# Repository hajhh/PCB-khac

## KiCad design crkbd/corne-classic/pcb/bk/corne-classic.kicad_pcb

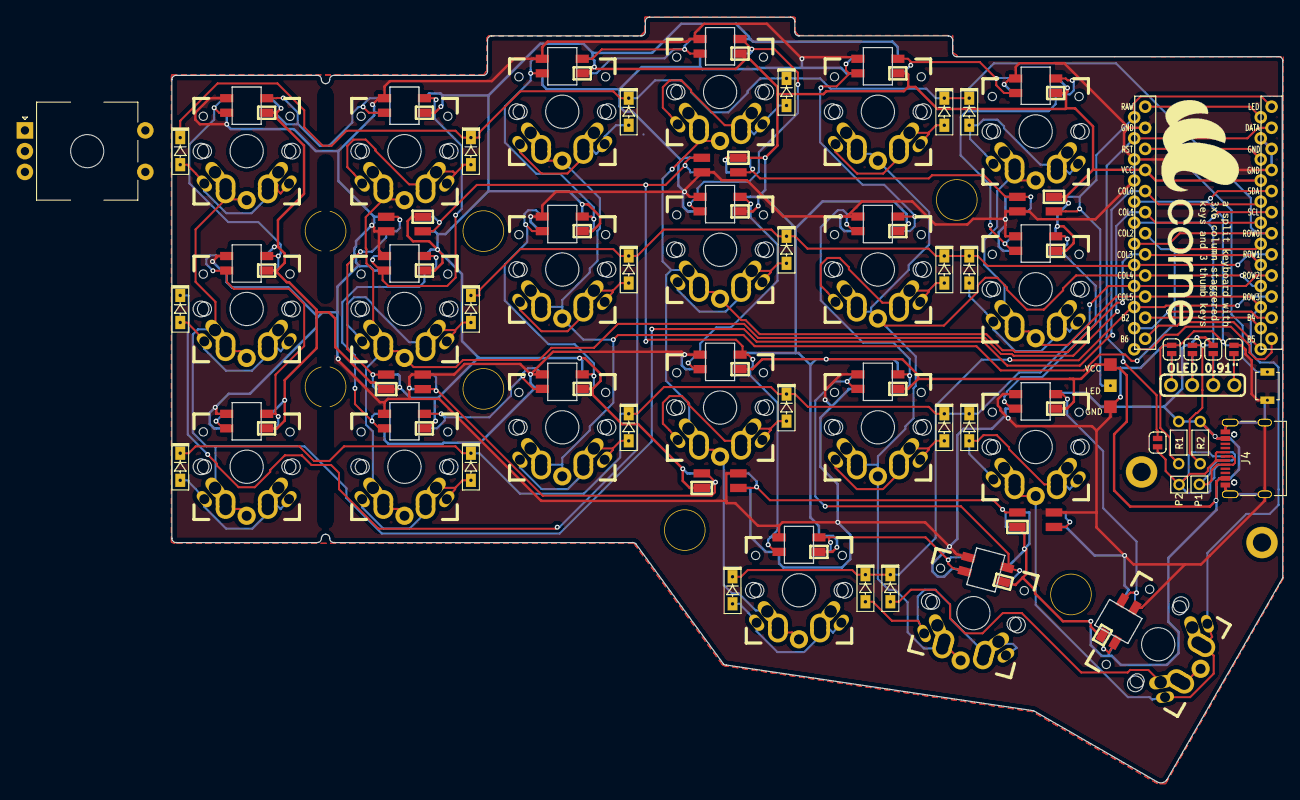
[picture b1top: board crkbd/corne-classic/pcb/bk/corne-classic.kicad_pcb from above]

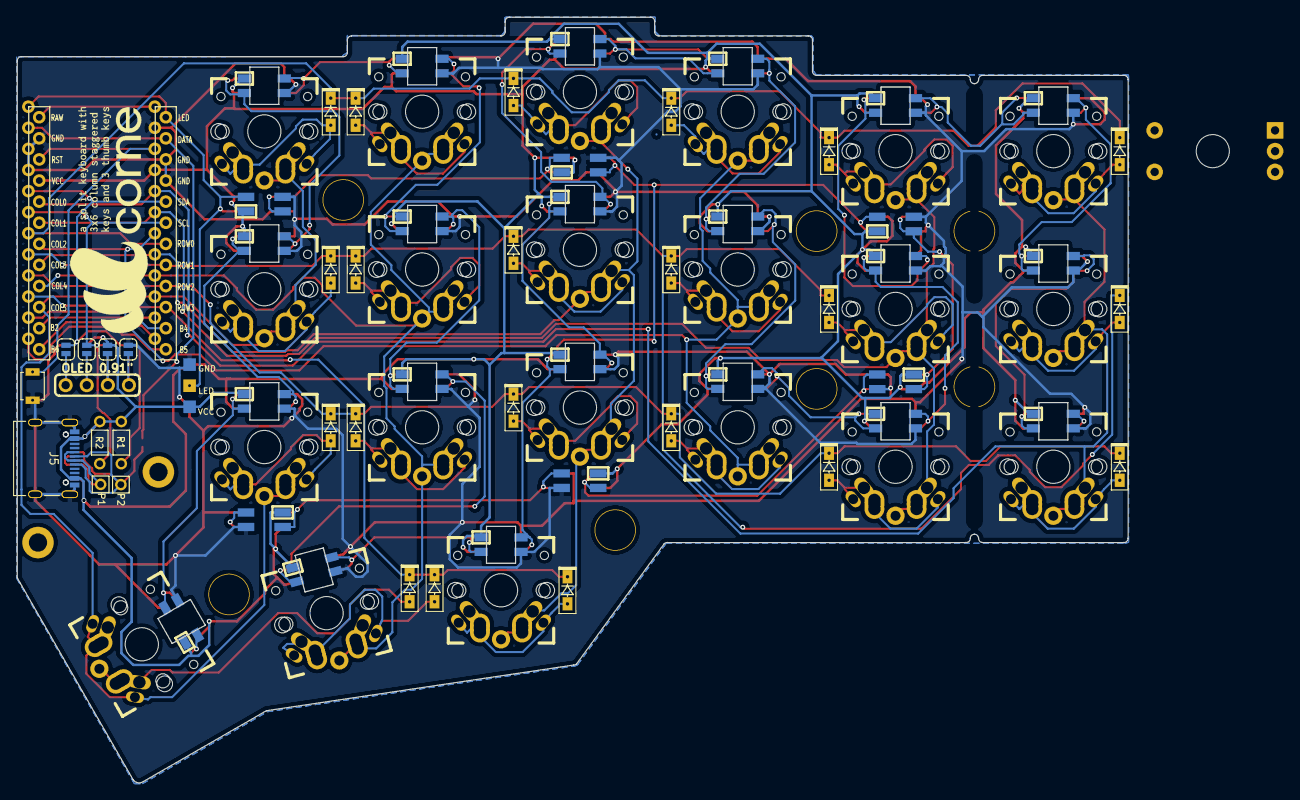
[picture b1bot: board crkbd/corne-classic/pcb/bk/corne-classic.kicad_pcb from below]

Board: 2 copper layers, 133.8 x 92.2 mm, 104 parts (7 on the bottom side), 68 nets.

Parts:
D1, D2, D3, D4, D5, D6, D7, D8, D9, D10, D11, D12, D13, D14, D15, D16, D17, D18, D19, D20, D21: D; Diode_smd
H1, H2: Hole_M2
H3, H4, H5, H6, H7, H8, H9: HOLE
H10, H11: logo
H12, H13, H14, H15: hole2
J2: OLED; OLED_SPILT
J3: LED; StripLED_rev
J4, J5: USB_C_Receptacle_Palconn_UTC16-G
JP1, JP2, JP3, JP4, JP5, JP6, JP7, JP8, JP9: jp
L1, L2, L3, L4, L5, L6: SK6812MINI; SK6812MINI_underglow_rev
L7, L8, L9, L10, L11, L12, L13, L14, L15, L16, L17, L18, L19, L20, L21, L22, L23, L24, L25, L26, L27: SK6812MINI; SK6812MINI_rev
P1, P2: i2c-pin; 1pin_conn
R1, R2: R
RSW1: SW_PUSH; SW_SPST_B3U-1000P
SW1, SW2, SW3, SW4, SW5, SW6, SW7, SW8, SW9, SW10, SW11, SW12, SW13, SW14, SW15, SW16, SW17, SW18, SW19, SW20: SW_PUSH; 1u
SW21: SW_PUSH; 1.75u
SW22: Rotary_Encoder_Switch; Rotary_econder
U1: ProMicro; ProMicro_v2

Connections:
GND: J3.1, J4.A1, J4.A12, J4.B1, J4.B12, J4.S1, J5.A1, J5.A12, J5.B1, J5.B12, J5.S1, JP2.1, JP9.1, L1.2, L2.2, L3.2, L4.2, L5.2, L6.2, L7.2, L8.2, L9.2, L10.2, L11.2, L12.2, L13.2, L14.2, L15.2, L16.2, L17.2, L18.2, L19.2, L20.2, L21.2, L22.2, L23.2, L24.2, L25.2, L26.2, L27.2, RSW1.2, U1.3, U1.4, U1.23
LED: J3.2, L3.3, U1.1
unnamed: D1.2, SW1.2
unnamed: D2.2, SW2.2
unnamed: D3.2, SW3.2
unnamed: D4.2, SW4.2
unnamed: D5.2, SW5.2
unnamed: D6.2, SW6.2
unnamed: D7.2, SW7.2
unnamed: D8.2, SW8.2
unnamed: D9.2, SW9.2
unnamed: D10.2, SW10.2
unnamed: D11.2, SW11.2
unnamed: D12.2, SW12.2
unnamed: D13.2, SW13.2
unnamed: D14.2, SW14.2
unnamed: D15.2, SW15.2
unnamed: D16.2, SW16.2
unnamed: D17.2, SW17.2
unnamed: D18.2, SW18.2
unnamed: D19.2, SW19.2
unnamed: D20.2, SW20.2
unnamed: D21.2, SW21.2
unnamed: J2.1, JP5.2, JP9.2
unnamed: J2.2, JP4.2, JP8.2
unnamed: J2.3, JP3.2, JP7.2
unnamed: J2.4, JP2.2, JP6.2
unnamed: J4.A6, J4.B6, J5.A6, J5.B6, JP1.2, P2.1
unnamed: J4.A7, J4.B7, J5.A7, J5.B7, P1.1
unnamed: L7.3, L8.1
unnamed: L9.3, L10.1
unnamed: L10.3, L16.1
unnamed: L11.1, L17.3
unnamed: L11.3, L12.1
unnamed: L12.3, L18.1
unnamed: L13.1, L19.3
unnamed: L7.1, L13.3
unnamed: L8.3, L14.1
unnamed: L14.3, L20.1
unnamed: L15.1, L21.3
unnamed: L9.1, L15.3
unnamed: L16.3, L22.1
unnamed: L17.1, L23.3
unnamed: L18.3, L24.1
unnamed: L20.3, L21.1
unnamed: L1.1, L4.3
unnamed: L1.3, L2.1, L22.3, L25.1
unnamed: L23.1, L26.3
unnamed: L2.3, L3.1
unnamed: L24.3, L27.1
unnamed: L4.1, L5.3
unnamed: L25.3, L26.1
unnamed: L5.1, L6.3
SCL: JP4.1, JP7.1, R2.2, U1.6
SDA: JP5.1, JP6.1, R1.2, U1.5
VCC: J3.3, J4.A4, J4.A9, J4.B4, J4.B9, J5.A4, J5.A9, J5.B4, J5.B9, JP3.1, JP8.1, L1.4, L2.4, L3.4, L4.4, L5.4, L6.4, L7.4, L8.4, L9.4, L10.4, L11.4, L12.4, L13.4, L14.4, L15.4, L16.4, L17.4, L18.4, L19.4, L20.4, L21.4, L22.4, L23.4, L24.4, L25.4, L26.4, L27.4, R1.1, R2.1, U1.21
col0: SW1.1, SW7.1, SW13.1, U1.20
col1: SW2.1, SW8.1, SW14.1, U1.19
col2: SW3.1, SW9.1, SW15.1, U1.18
col3: SW4.1, SW10.1, SW16.1, SW19.1, U1.17
col4: SW5.1, SW11.1, SW17.1, SW20.1, U1.16
col5: SW6.1, SW12.1, SW18.1, SW21.1, U1.15
data: JP1.1, U1.2
reset: RSW1.1, U1.22
row0: D1.1, D2.1, D3.1, D4.1, D5.1, D6.1, U1.7
row1: D7.1, D8.1, D9.1, D10.1, D11.1, D12.1, U1.8
row2: D13.1, D14.1, D15.1, D16.1, D17.1, D18.1, U1.9
row3: D19.1, D20.1, D21.1, U1.10

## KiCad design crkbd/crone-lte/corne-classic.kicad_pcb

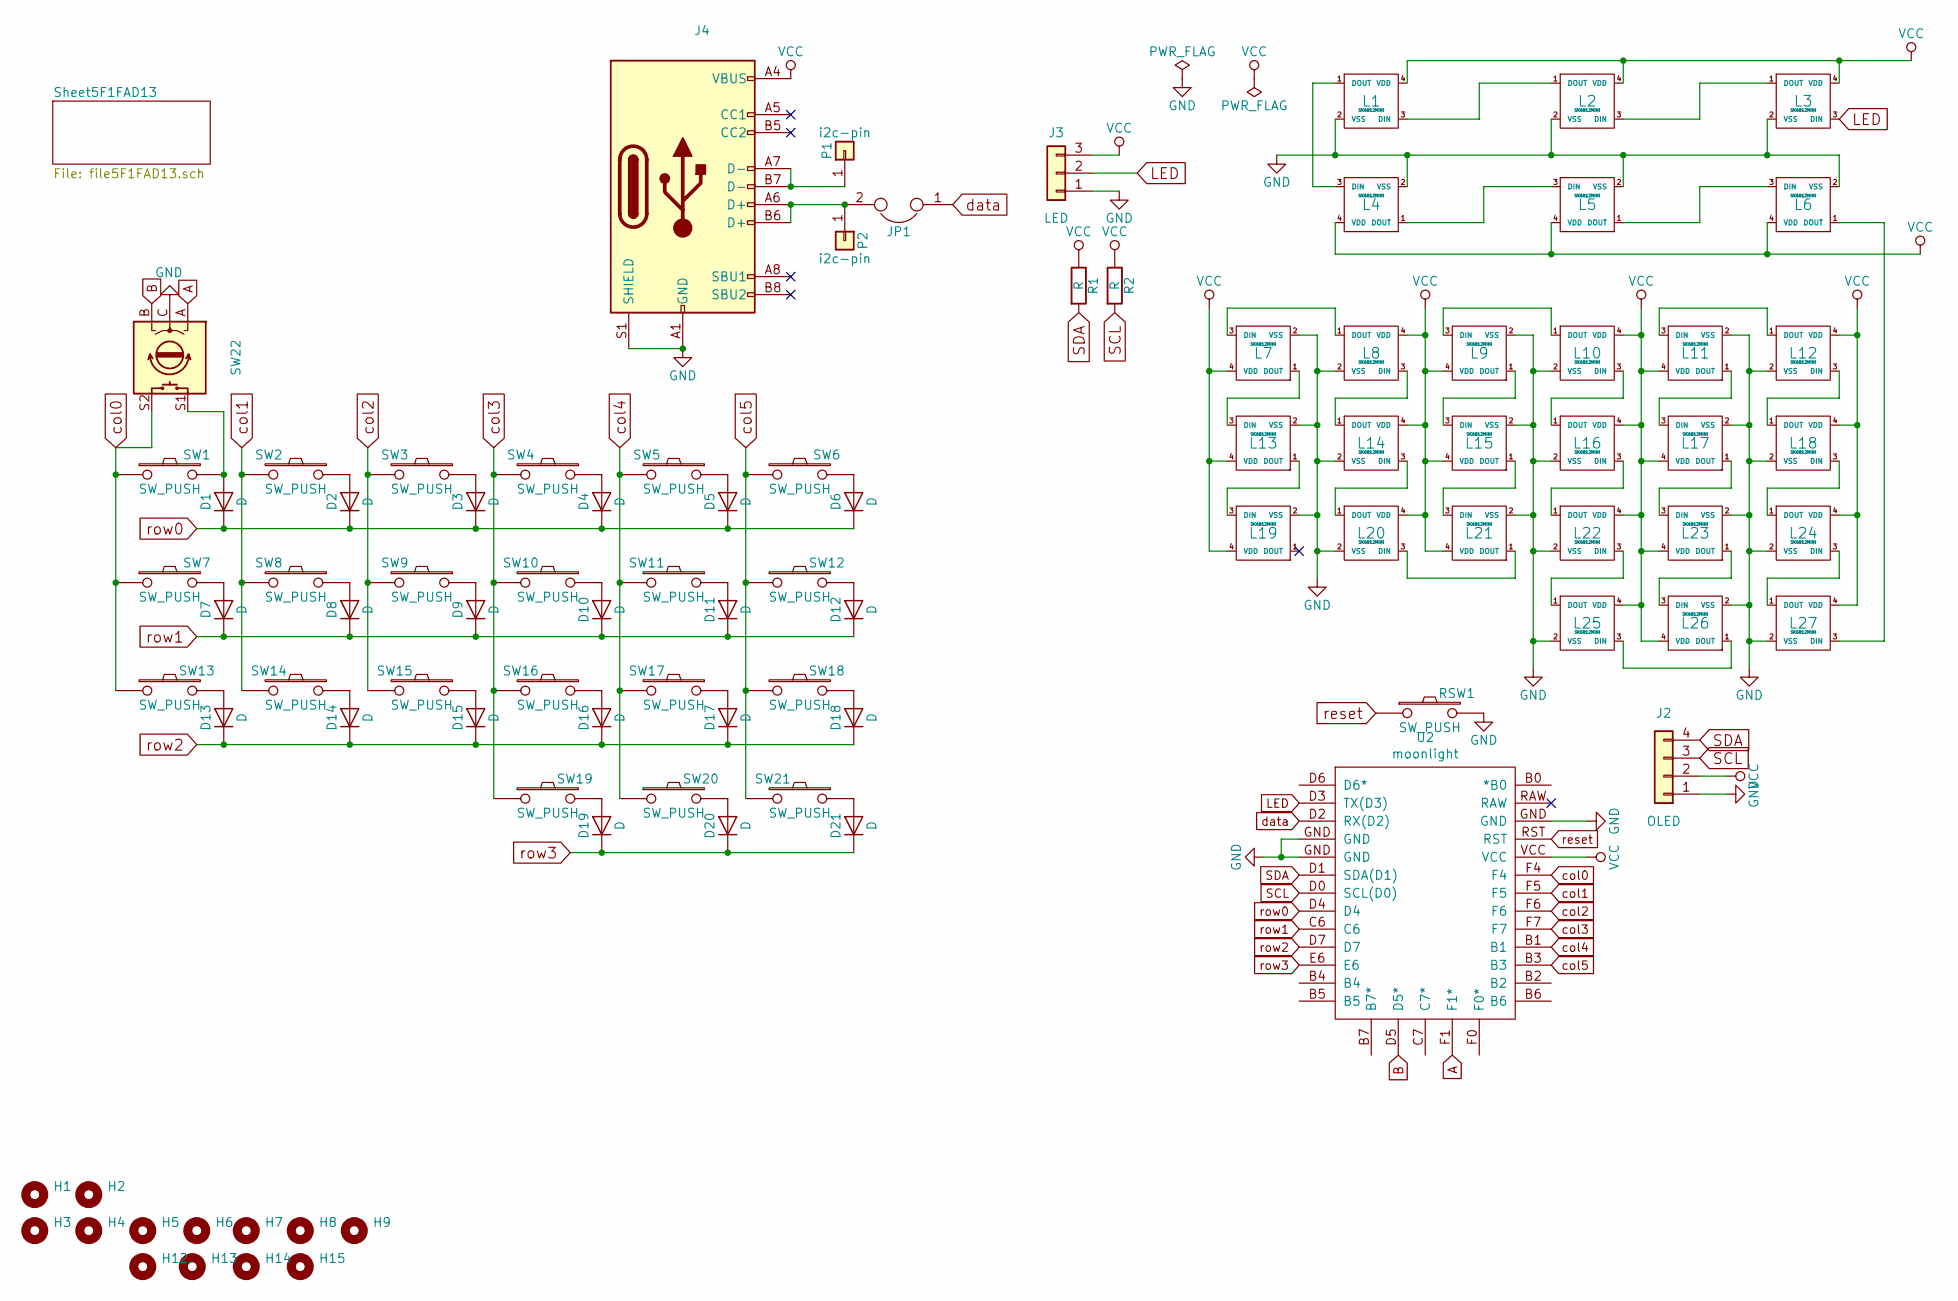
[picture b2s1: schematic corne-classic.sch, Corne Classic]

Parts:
D1, D2, D3, D4, D5, D6, D7, D8, D9, D10, D11, D12, D13, D14, D15, D16, D17, D18, D19, D20, D21: D
H1, H2: Hole_M2
H3, H4, H5, H6, H7, H8, H9: HOLE
H12, H13, H14, H15: hole2
J2: OLED; OLED_0.91'_FONTSIDE
J3: LED; LED-strip
J4: USB_C_Receptacle_Palconn_UTC16-G
JP1: jp
L1, L2, L3, L4, L5, L6: SK6812MINI; SK6812-BOARD
L7, L8, L9, L10, L11, L12, L13, L14, L15, L16, L17, L18, L19, L20, L21, L22, L23, L24, L25, L26, L27: SK6812MINI; SK6812-SW
P1, P2: i2c-pin; pin
R1, R2: R
RSW1: SW_PUSH; SW_SPST_B3U-1000P
SW1, SW2, SW3, SW4, SW5, SW6, SW7, SW8, SW9, SW10, SW11, SW12, SW13, SW14, SW15, SW16, SW17, SW18, SW19, SW20: SW_PUSH; 1u
SW21: SW_PUSH; 1.75u
SW22: Rotary_econder
U2: moonlight

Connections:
A: SW22.A, U2.F1 (F1*)
B: SW22.B, U2.D5 (D5*)
GND: J2.1, J3.1, J4.A1 (GND), J4.A12 (GND), J4.B1 (GND), J4.B12 (GND), J4.S1 (SHIELD), L1.2 (VSS), L2.2 (VSS), L3.2 (VSS), L4.2 (VSS), L5.2 (VSS), L6.2 (VSS), L7.2 (VSS), L8.2 (VSS), L9.2 (VSS), L10.2 (VSS), L11.2 (VSS), L12.2 (VSS), L13.2 (VSS), L14.2 (VSS), L15.2 (VSS), L16.2 (VSS), L17.2 (VSS), L18.2 (VSS), L19.2 (VSS), L20.2 (VSS), L21.2 (VSS), L22.2 (VSS), L23.2 (VSS), L24.2 (VSS), L25.2 (VSS), L26.2 (VSS), L27.2 (VSS), RSW1.2, SW22.C, U2.GND
LED: J3.2, L3.3 (DIN), U2.D3 (TX(D3))
unnamed: D1.2 (A), SW1.2, SW22.S1
unnamed: D2.2 (A), SW2.1
unnamed: D3.2 (A), SW3.1
unnamed: D4.2 (A), SW4.1
unnamed: D5.2 (A), SW5.1
unnamed: D6.2 (A), SW6.2
unnamed: D7.2 (A), SW7.2
unnamed: D8.2 (A), SW8.1
unnamed: D9.2 (A), SW9.1
unnamed: D10.2 (A), SW10.1
unnamed: D11.2 (A), SW11.1
unnamed: D12.2 (A), SW12.2
unnamed: D13.2 (A), SW13.2
unnamed: D14.2 (A), SW14.1
unnamed: D15.2 (A), SW15.1
unnamed: D16.2 (A), SW16.1
unnamed: D17.2 (A), SW17.1
unnamed: D18.2 (A), SW18.2
unnamed: D19.2 (A), SW19.2
unnamed: D20.2 (A), SW20.2
unnamed: D21.2 (A), SW21.1
unnamed: J4.A6 (D+), J4.B6 (D+), JP1.2, P2.1
unnamed: J4.A7 (D-), J4.B7 (D-), P1.1
unnamed: L1.1 (DOUT), L4.3 (DIN)
unnamed: L1.3 (DIN), L2.1 (DOUT)
unnamed: L2.3 (DIN), L3.1 (DOUT)
unnamed: L4.1 (DOUT), L5.3 (DIN)
unnamed: L5.1 (DOUT), L6.3 (DIN)
unnamed: L7.3 (DIN), L8.1 (DOUT)
unnamed: L9.3 (DIN), L10.1 (DOUT)
unnamed: L10.3 (DIN), L16.1 (DOUT)
unnamed: L11.1 (DOUT), L17.3 (DIN)
unnamed: L11.3 (DIN), L12.1 (DOUT)
unnamed: L12.3 (DIN), L18.1 (DOUT)
unnamed: L13.1 (DOUT), L19.3 (DIN)
unnamed: L7.1 (DOUT), L13.3 (DIN)
unnamed: L8.3 (DIN), L14.1 (DOUT)
unnamed: L14.3 (DIN), L20.1 (DOUT)
unnamed: L15.1 (DOUT), L21.3 (DIN)
unnamed: L9.1 (DOUT), L15.3 (DIN)
unnamed: L16.3 (DIN), L22.1 (DOUT)
unnamed: L17.1 (DOUT), L23.3 (DIN)
unnamed: L18.3 (DIN), L24.1 (DOUT)
unnamed: L20.3 (DIN), L21.1 (DOUT)
unnamed: L22.3 (DIN), L25.1 (DOUT)
unnamed: L23.1 (DOUT), L26.3 (DIN)
unnamed: L24.3 (DIN), L27.1 (DOUT)
unnamed: L25.3 (DIN), L26.1 (DOUT)
unnamed: L6.1 (DOUT), L27.3 (DIN)
SCL: J2.3, R2.2, U2.D0 (SCL(D0))
SDA: J2.4, R1.2, U2.D1 (SDA(D1))
VCC: J2.2, J3.3, J4.A4 (VBUS), J4.A9 (VBUS), J4.B4 (VBUS), J4.B9 (VBUS), L1.4 (VDD), L2.4 (VDD), L3.4 (VDD), L4.4 (VDD), L5.4 (VDD), L6.4 (VDD), L7.4 (VDD), L8.4 (VDD), L9.4 (VDD), L10.4 (VDD), L11.4 (VDD), L12.4 (VDD), L13.4 (VDD), L14.4 (VDD), L15.4 (VDD), L16.4 (VDD), L17.4 (VDD), L18.4 (VDD), L19.4 (VDD), L20.4 (VDD), L21.4 (VDD), L22.4 (VDD), L23.4 (VDD), L24.4 (VDD), L25.4 (VDD), L26.4 (VDD), L27.4 (VDD), R1.1, R2.1, U2.VCC
col0: SW1.1, SW7.1, SW13.1, SW22.S2, U2.F4
col1: SW2.2, SW8.2, SW14.2, U2.F5
col2: SW3.2, SW9.2, SW15.2, U2.F6
col3: SW4.2, SW10.2, SW16.2, SW19.1, U2.F7
col4: SW5.2, SW11.2, SW17.2, SW20.1, U2.B1
col5: SW6.1, SW12.1, SW18.1, SW21.2, U2.B3
data: JP1.1, U2.D2 (RX(D2))
reset: RSW1.1, U2.RST
row0: D1.1 (K), D2.1 (K), D3.1 (K), D4.1 (K), D5.1 (K), D6.1 (K), U2.D4
row1: D7.1 (K), D8.1 (K), D9.1 (K), D10.1 (K), D11.1 (K), D12.1 (K), U2.C6
row2: D13.1 (K), D14.1 (K), D15.1 (K), D16.1 (K), D17.1 (K), D18.1 (K), U2.D7
row3: D19.1 (K), D20.1 (K), D21.1 (K), U2.E6

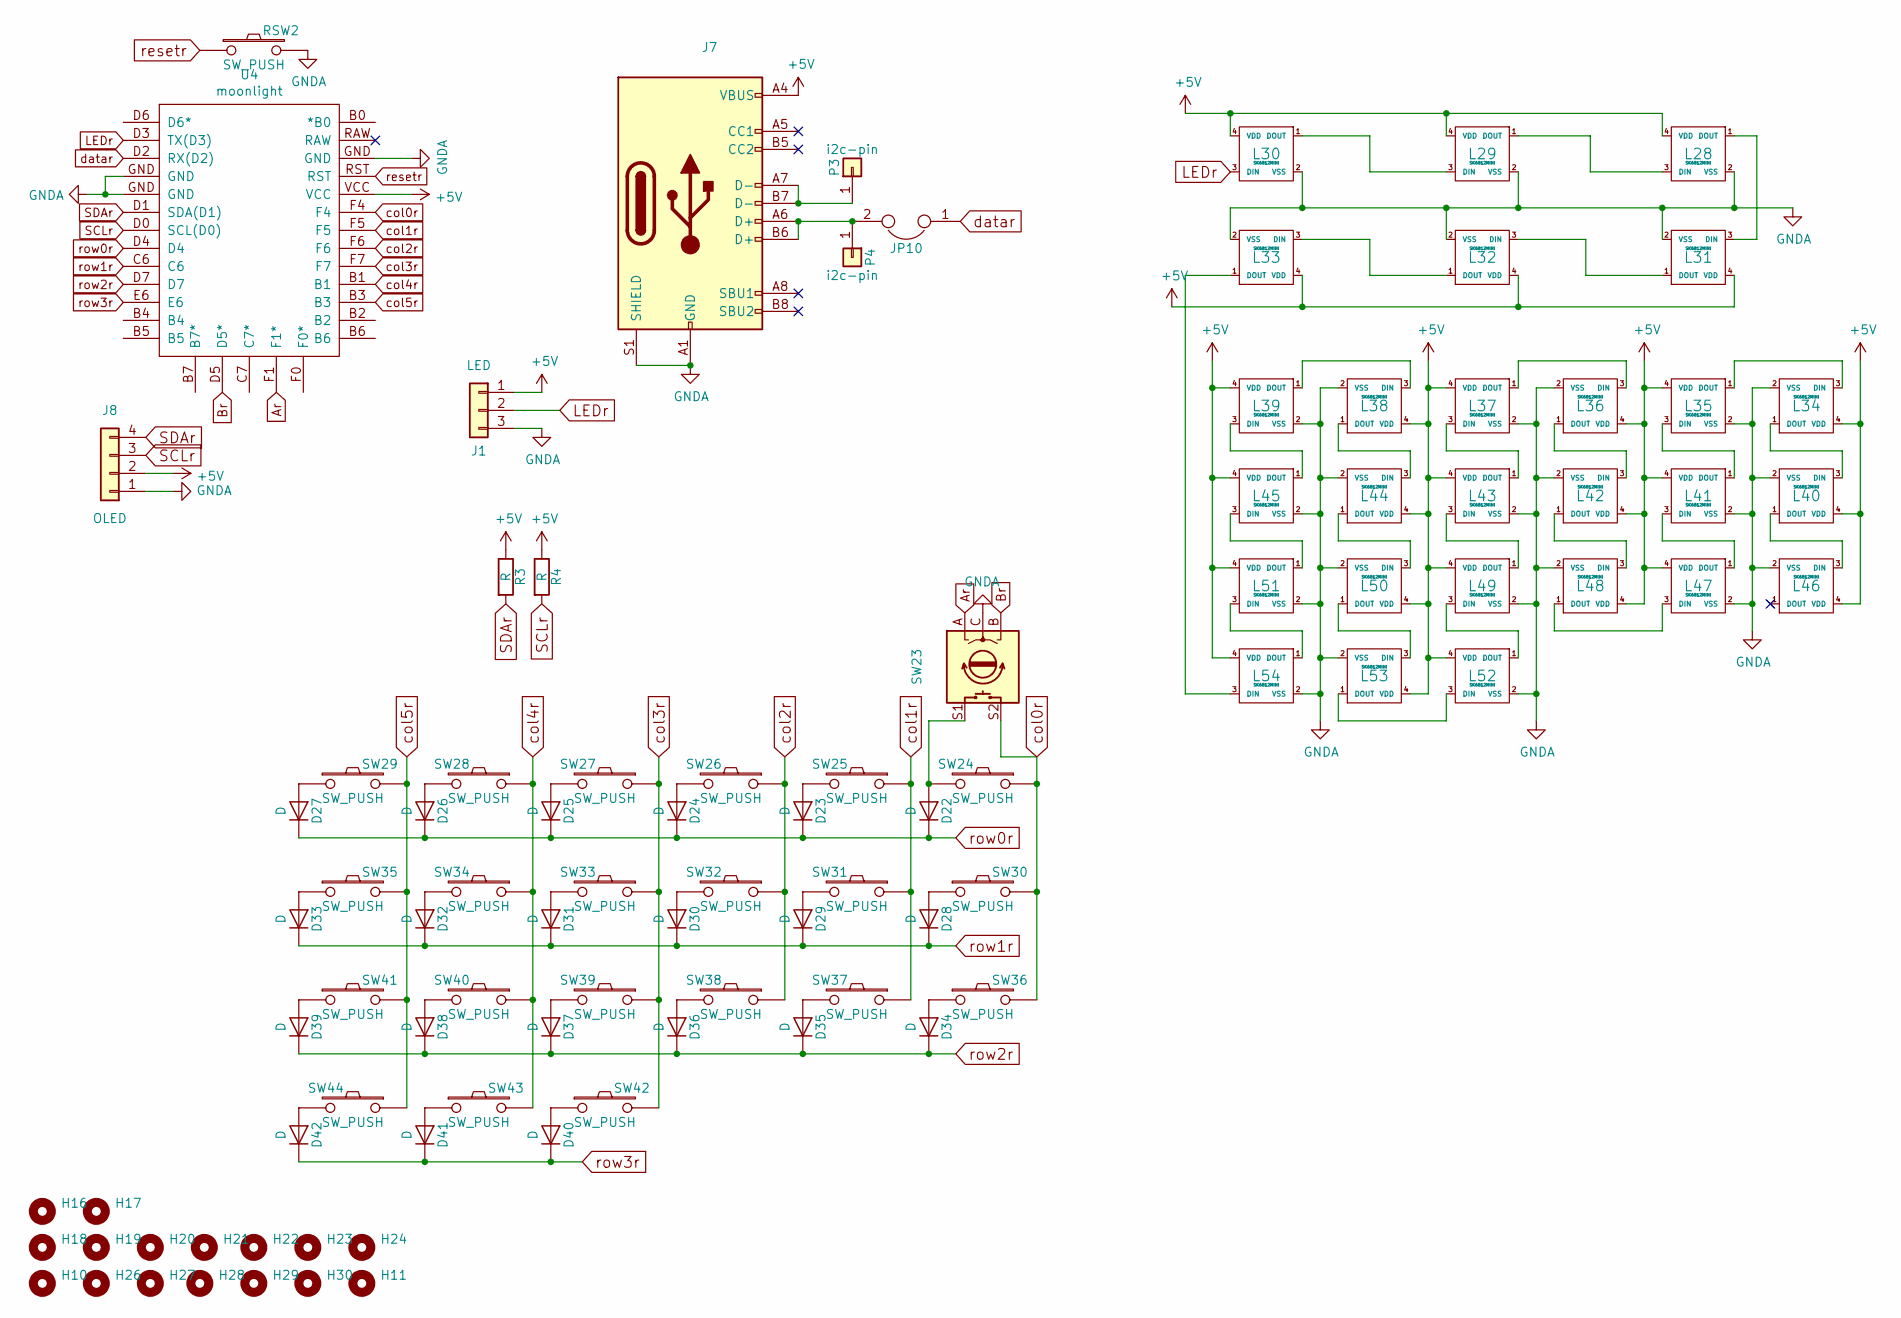
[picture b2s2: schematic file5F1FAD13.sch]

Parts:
D22, D23, D24, D25, D26, D27, D28, D29, D30, D31, D32, D33, D34, D35, D36, D37, D38, D39, D40, D41, D42: D
H10, H26: logo
H11, H27, H28, H29, H30: hole2
H16, H17: Hole_M2
H18, H19, H20, H21, H22, H23, H24: HOLE
J1: LED; LED-strip
J7: USB_C_Receptacle_Palconn_UTC16-G
J8: OLED; OLED_0.91'_FONTSIDE
JP10: jp
L28, L29, L30, L31, L32, L33: SK6812MINI; SK6812-BOARD
L34, L35, L36, L37, L38, L39, L40, L41, L42, L43, L44, L45, L46, L47, L48, L49, L50, L51, L52, L53, L54: SK6812MINI; SK6812-SW
P3, P4: i2c-pin; pin
R3, R4: R
RSW2: SW_PUSH; SW_SPST_B3U-1000P
SW23: Rotary_econder
SW24, SW25, SW26, SW27, SW28, SW29, SW30, SW31, SW32, SW33, SW34, SW35, SW36, SW37, SW38, SW39, SW40, SW41, SW42, SW43: SW_PUSH; 1u
SW44: SW_PUSH; 1.75u
U4: moonlight

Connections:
+5V: J1.1, J7.A4 (VBUS), J7.A9 (VBUS), J7.B4 (VBUS), J7.B9 (VBUS), J8.2, L28.4 (VDD), L29.4 (VDD), L30.4 (VDD), L31.4 (VDD), L32.4 (VDD), L33.4 (VDD), L34.4 (VDD), L35.4 (VDD), L36.4 (VDD), L37.4 (VDD), L38.4 (VDD), L39.4 (VDD), L40.4 (VDD), L41.4 (VDD), L42.4 (VDD), L43.4 (VDD), L44.4 (VDD), L45.4 (VDD), L46.4 (VDD), L47.4 (VDD), L48.4 (VDD), L49.4 (VDD), L50.4 (VDD), L51.4 (VDD), L52.4 (VDD), L53.4 (VDD), L54.4 (VDD), R3.1, R4.1, U4.VCC
Ar: SW23.A, U4.F1 (F1*)
Br: SW23.B, U4.D5 (D5*)
GNDA: J1.3, J7.A1 (GND), J7.A12 (GND), J7.B1 (GND), J7.B12 (GND), J7.S1 (SHIELD), J8.1, L28.2 (VSS), L29.2 (VSS), L30.2 (VSS), L31.2 (VSS), L32.2 (VSS), L33.2 (VSS), L34.2 (VSS), L35.2 (VSS), L36.2 (VSS), L37.2 (VSS), L38.2 (VSS), L39.2 (VSS), L40.2 (VSS), L41.2 (VSS), L42.2 (VSS), L43.2 (VSS), L44.2 (VSS), L45.2 (VSS), L46.2 (VSS), L47.2 (VSS), L48.2 (VSS), L49.2 (VSS), L50.2 (VSS), L51.2 (VSS), L52.2 (VSS), L53.2 (VSS), L54.2 (VSS), RSW2.2, SW23.C, U4.GND
LEDr: J1.2, L30.3 (DIN), U4.D3 (TX(D3))
unnamed: D22.2 (A), SW23.S1, SW24.2
unnamed: D23.2 (A), SW25.2
unnamed: D24.2 (A), SW26.2
unnamed: D25.2 (A), SW27.2
unnamed: D26.2 (A), SW28.2
unnamed: D27.2 (A), SW29.1
unnamed: D28.2 (A), SW30.1
unnamed: D29.2 (A), SW31.2
unnamed: D30.2 (A), SW32.2
unnamed: D31.2 (A), SW33.2
unnamed: D32.2 (A), SW34.2
unnamed: D33.2 (A), SW35.1
unnamed: D34.2 (A), SW36.1
unnamed: D35.2 (A), SW37.2
unnamed: D36.2 (A), SW38.2
unnamed: D37.2 (A), SW39.2
unnamed: D38.2 (A), SW40.2
unnamed: D39.2 (A), SW41.1
unnamed: D40.2 (A), SW42.1
unnamed: D41.2 (A), SW43.1
unnamed: D42.2 (A), SW44.2
unnamed: J7.A6 (D+), J7.B6 (D+), JP10.2, P4.1
unnamed: J7.A7 (D-), J7.B7 (D-), P3.1
unnamed: L28.1 (DOUT), L31.3 (DIN)
unnamed: L28.3 (DIN), L29.1 (DOUT)
unnamed: L29.3 (DIN), L30.1 (DOUT)
unnamed: L31.1 (DOUT), L32.3 (DIN)
unnamed: L32.1 (DOUT), L33.3 (DIN)
unnamed: L33.1 (DOUT), L54.3 (DIN)
unnamed: L34.1 (DOUT), L40.3 (DIN)
unnamed: L34.3 (DIN), L35.1 (DOUT)
unnamed: L35.3 (DIN), L41.1 (DOUT)
unnamed: L36.1 (DOUT), L42.3 (DIN)
unnamed: L36.3 (DIN), L37.1 (DOUT)
unnamed: L37.3 (DIN), L43.1 (DOUT)
unnamed: L38.1 (DOUT), L44.3 (DIN)
unnamed: L38.3 (DIN), L39.1 (DOUT)
unnamed: L39.3 (DIN), L45.1 (DOUT)
unnamed: L40.1 (DOUT), L46.3 (DIN)
unnamed: L41.3 (DIN), L47.1 (DOUT)
unnamed: L42.1 (DOUT), L48.3 (DIN)
unnamed: L43.3 (DIN), L49.1 (DOUT)
unnamed: L44.1 (DOUT), L50.3 (DIN)
unnamed: L45.3 (DIN), L51.1 (DOUT)
unnamed: L47.3 (DIN), L48.1 (DOUT)
unnamed: L49.3 (DIN), L52.1 (DOUT)
unnamed: L50.1 (DOUT), L53.3 (DIN)
unnamed: L51.3 (DIN), L54.1 (DOUT)
unnamed: L52.3 (DIN), L53.1 (DOUT)
SCLr: J8.3, R4.2, U4.D0 (SCL(D0))
SDAr: J8.4, R3.2, U4.D1 (SDA(D1))
col0r: SW23.S2, SW24.1, SW30.2, SW36.2, U4.F4
col1r: SW25.1, SW31.1, SW37.1, U4.F5
col2r: SW26.1, SW32.1, SW38.1, U4.F6
col3r: SW27.1, SW33.1, SW39.1, SW42.2, U4.F7
col4r: SW28.1, SW34.1, SW40.1, SW43.2, U4.B1
col5r: SW29.2, SW35.2, SW41.2, SW44.1, U4.B3
datar: JP10.1, U4.D2 (RX(D2))
resetr: RSW2.1, U4.RST
row0r: D22.1 (K), D23.1 (K), D24.1 (K), D25.1 (K), D26.1 (K), D27.1 (K), U4.D4
row1r: D28.1 (K), D29.1 (K), D30.1 (K), D31.1 (K), D32.1 (K), D33.1 (K), U4.C6
row2r: D34.1 (K), D35.1 (K), D36.1 (K), D37.1 (K), D38.1 (K), D39.1 (K), U4.D7
row3r: D40.1 (K), D41.1 (K), D42.1 (K), U4.E6

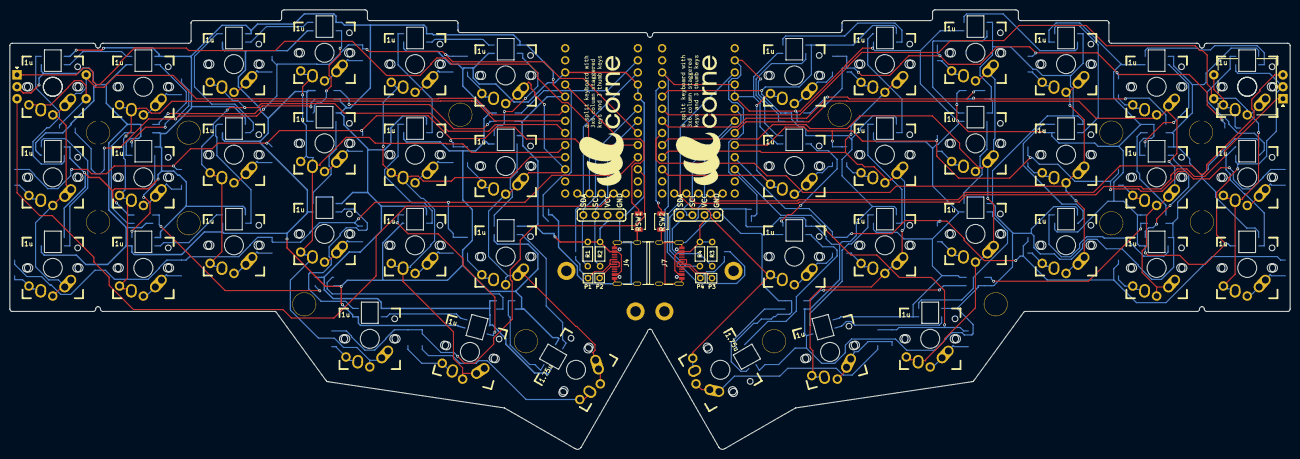
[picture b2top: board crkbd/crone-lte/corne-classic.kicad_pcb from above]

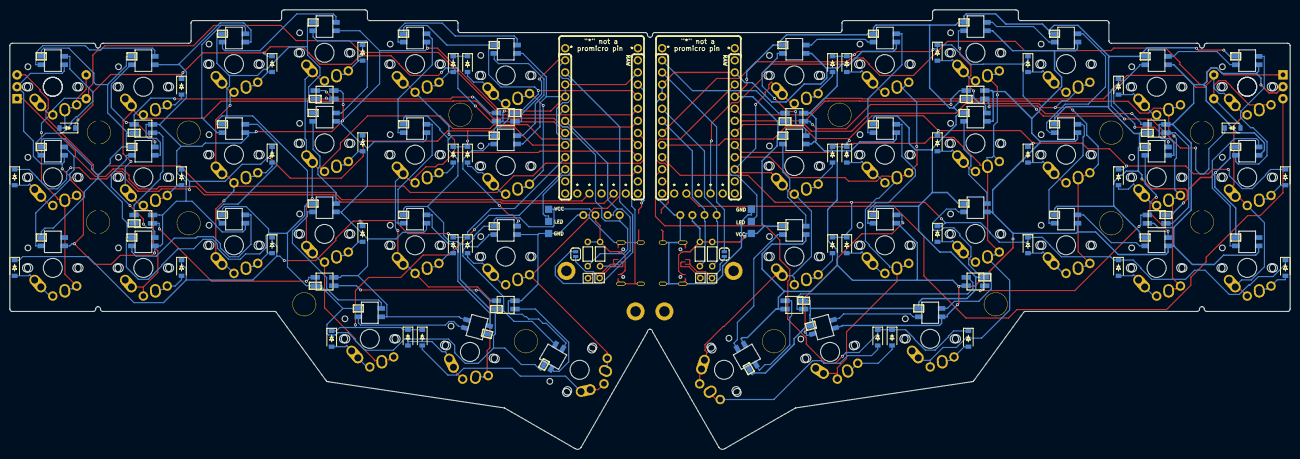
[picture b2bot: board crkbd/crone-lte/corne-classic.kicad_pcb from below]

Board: 2 copper layers, 268.6 x 92.2 mm, 189 parts (59 on the bottom side), 136 nets.

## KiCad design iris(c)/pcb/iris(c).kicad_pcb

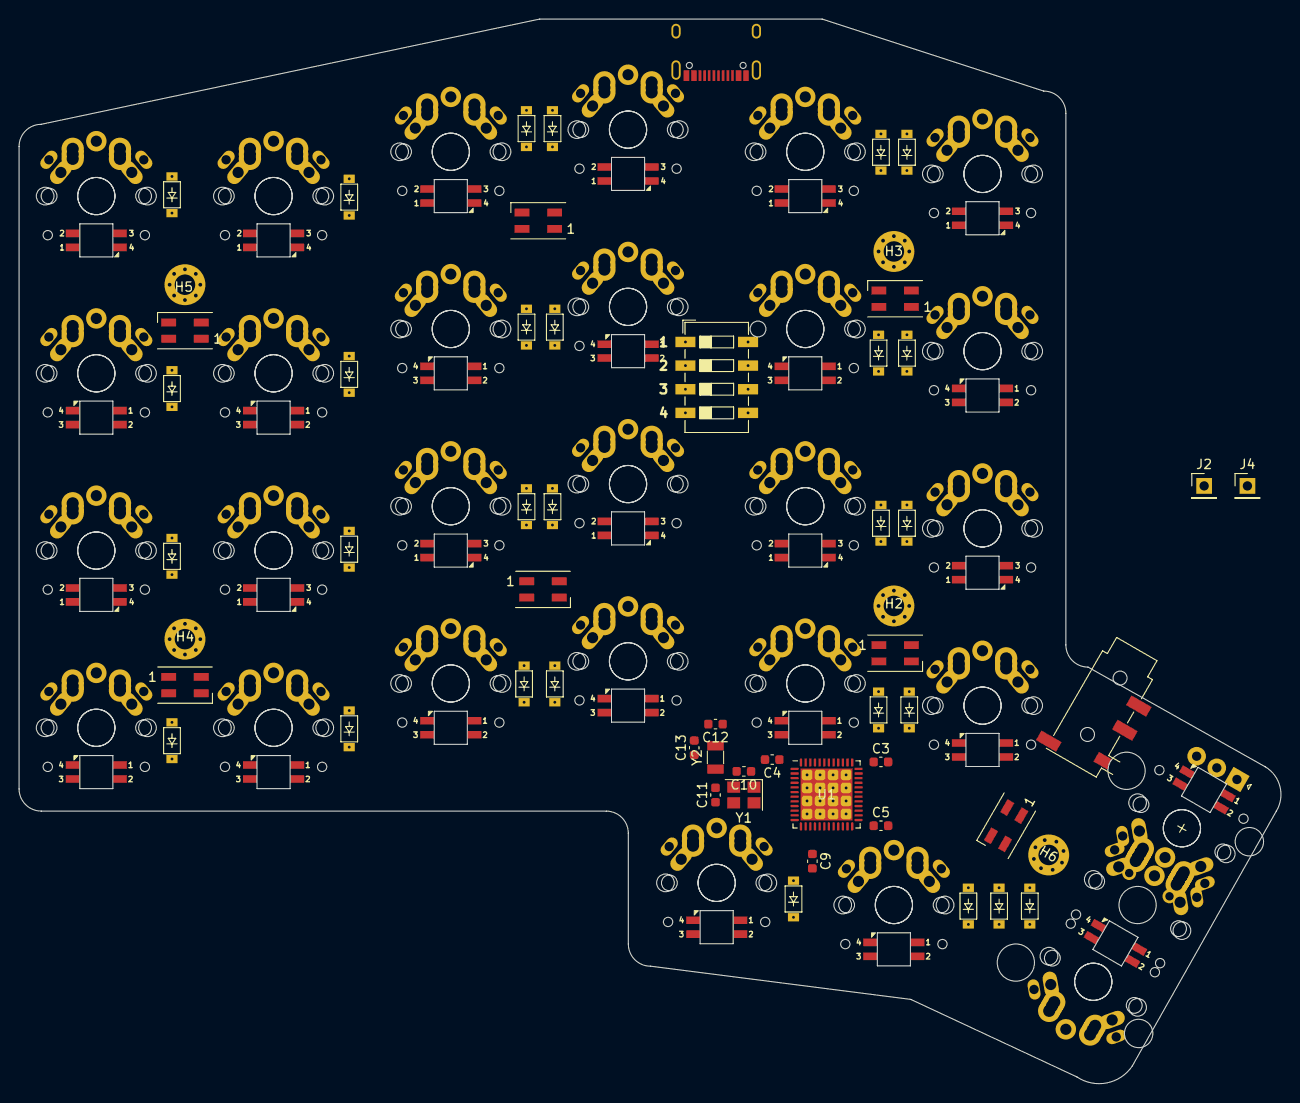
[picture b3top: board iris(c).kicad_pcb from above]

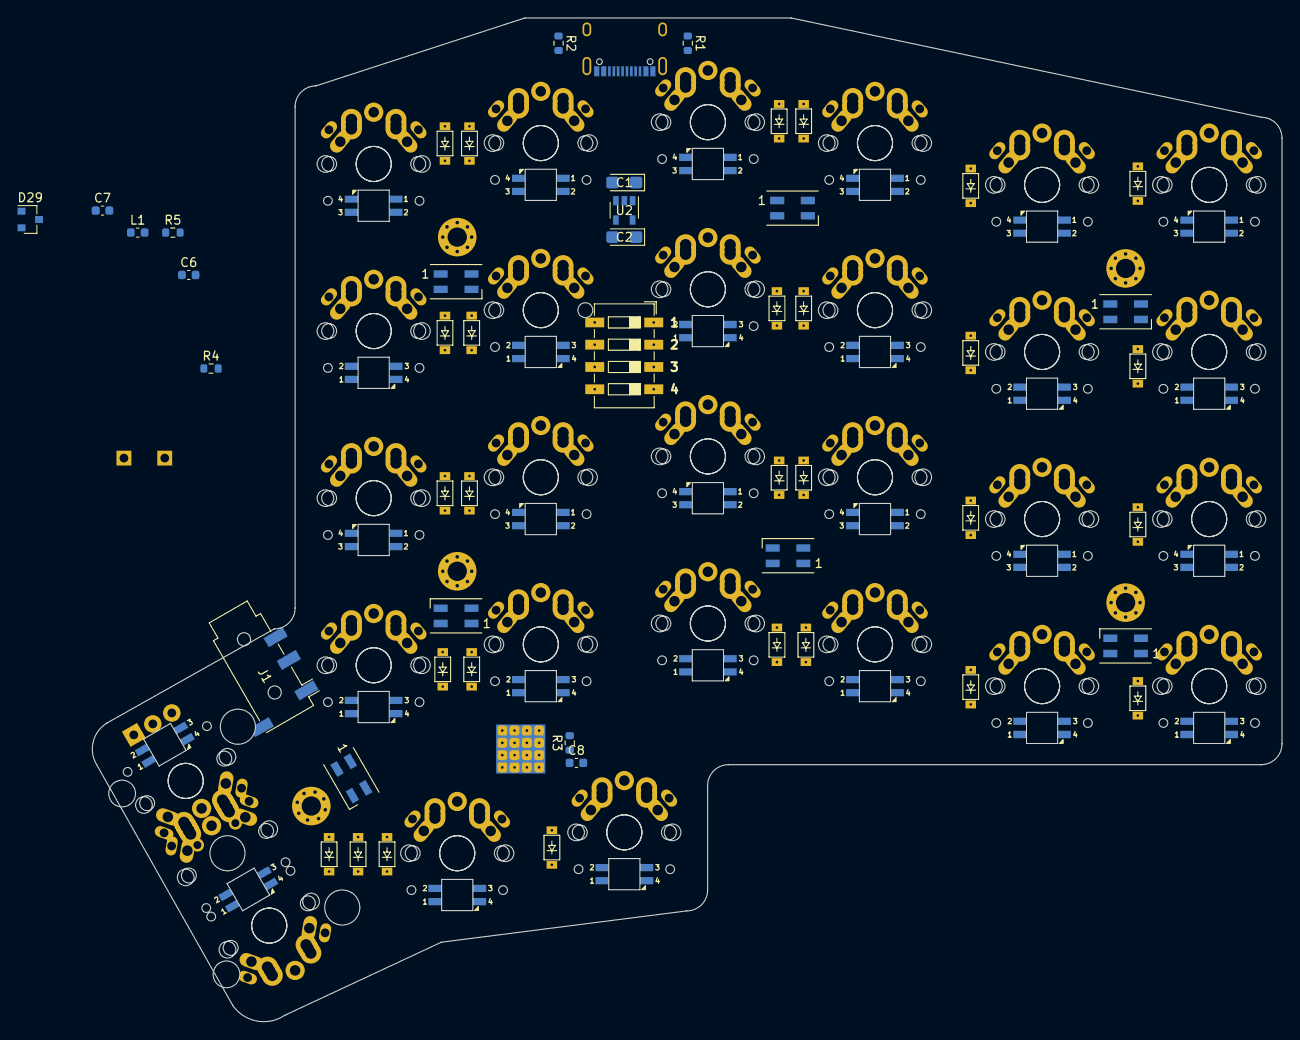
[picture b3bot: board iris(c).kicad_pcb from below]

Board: 2 copper layers, 135.6 x 114.4 mm, 128 parts (15 on the bottom side), 91 nets, no tracks yet.

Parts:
C1, C2: CP1_Small; CP_EIA-3216-10_Kemet-I
C3, C4, C5, C6, C7, C8: 100nF; C_0603_1608Metric
C9: 2.2uF; C_0603_1608Metric
C10, C11, C12, C13: C_0603_1608Metric
D1, D2, D3, D4, D5, D6, D7, D8, D9, D10, D11, D12, D13, D14, D15, D16, D17, D18, D19, D20, D21, D22, D23, D24, D25, D26, D27, D28: DIODE
D29: BAT54C; SOT-23
H1: Stab
H2, H3, H4, H5, H6: MountingHole_2.2mm_M2_Pad_Via
J1: Conn_01x04; Jack_3.5mm_PJ320D_Horizontal
J2, J4: PinHeader_1x01_P2.54mm_Vertical
J3: USB-C-16pin-hight
L1: 1Kr-100Mhz; L_0603_1608Metric
LED1, LED2, LED3, LED4, LED5, LED6, LED7: SK6812MINI-FLIP
LED8, LED9, LED10, LED11, LED12, LED13, LED20, LED21, LED22, LED23, LED24, LED25, LED32, LED33: sk6812mini-e(r2l)
LED14, LED15, LED16, LED17, LED18, LED19, LED26, LED27, LED28, LED29, LED30, LED31, LED34, LED35: sk6812mini-e(l2r)
R1, R2: 5k1; R_0603_1608Metric
R3, R4, R5: 10K; R_0603_1608Metric
SW1, SW2, SW3, SW4, SW5, SW6, SW7, SW8, SW9, SW10, SW11, SW12, SW14, SW15, SW16, SW17, SW18, SW19, SW20, SW21, SW22, SW23, SW24, SW25, SW27, SW28, SW29, SW30: SW-1u-Aps-Split
SW13: config; SW_DIP_SPSTx04_Slide_6.7x11.72mm_W6.73mm_P2.54mm_LowProfile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
SW26: SW_Push; SW-1u-Aps-Split
SW31: Econder
U1: QFN-48-1EP_7x7mm_P0.5mm_EP5.6x5.6mm
U2: MIC5219-3.3YM5; SOT-23-5
Y1: 25Mhz; Crystal_SMD_3225-4Pin_3.2x2.5mm
Y2: 32.768Khz; Crystal_SMD_3215-2Pin_3.2x1.5mm

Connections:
/MCU/DFU: R4.2, U1.44
/MCU/NRST: C8.1, R3.1, U1.7
/glow/glow-out: LED7.O, LED13.I
/matrix/matrix-out: LED32.O, LED33.O
D+: J3.A6, J3.B6, U1.33
D-: J3.A7, J3.B7, U1.32
GND: C1.2, C2.2, C3.2, C4.2, C5.2, C6.2, C7.2, C8.2, C9.2, C10.2, C11.2, C12.2, C13.2, J3.A1, J3.A12, J3.B1, J3.B12, J3.S1, J4.1, LED1.-, LED2.-, LED3.-, LED4.-, LED5.-, LED6.-, LED7.-, LED8.-, LED9.-, LED10.-, LED11.-, LED12.-, LED13.-, LED14.-, LED15.-, LED16.-, LED17.-, LED18.-, LED19.-, LED20.-, LED21.-, LED22.-, LED23.-, LED24.-, LED25.-, LED26.-, LED27.-, LED28.-, LED29.-, LED30.-, LED31.-, LED32.-, LED33.-, LED34.-, LED35.-, R1.1, R2.1, R4.1, R5.2, SW31.C, U1.8, U1.23, U1.35, U1.47, U1.49, U2.2, Y1.2, Y1.4
unnamed: C7.1, D29.3, U1.1
unnamed: C9.1, U1.22
unnamed: C10.1, U1.5, Y1.1
unnamed: C11.1, U1.6, Y1.3
unnamed: C12.1, U1.3, Y2.1
unnamed: C13.1, U1.4, Y2.2
unnamed: D1.1, D2.1, D3.1, D4.1, D5.1, D6.1
unnamed: D1.2, SW1.2
unnamed: D2.2, SW2.2
unnamed: D3.2, SW3.2
unnamed: D4.2, SW4.2
unnamed: D5.2, SW5.2
unnamed: D6.2, SW6.2
unnamed: D7.2, SW7.2
unnamed: D8.2, SW8.2
unnamed: D9.2, SW9.2
unnamed: D7.1, D8.1, D9.1, D10.1, D11.1, D12.1
unnamed: D10.2, SW10.2
unnamed: D11.2, SW11.2
unnamed: D12.2, SW12.2
unnamed: D13.1, D14.1, D15.1, D16.1, D17.1, D18.1
unnamed: D13.2, SW14.2
unnamed: D14.2, SW15.2
unnamed: D15.2, SW16.2
unnamed: D16.2, SW17.2
unnamed: D17.2, SW18.2
unnamed: D18.2, SW19.2
unnamed: D19.1, D20.1, D21.1, D22.1, D23.1, D24.1
unnamed: D19.2, SW20.2
unnamed: D20.2, SW21.2
unnamed: D21.2, SW22.2
unnamed: D22.2, SW23.2
unnamed: D23.2, SW24.2
unnamed: D24.2, SW25.2
unnamed: D25.1, D26.1, D27.1, D28.1
unnamed: D25.2, SW27.2
unnamed: D26.2, SW28.2
unnamed: D27.2, SW29.1
unnamed: D28.2, SW26.1, SW30.2, SW31.S1
unnamed: D29.2, J2.1
unnamed: J3.A5, R1.2
unnamed: J3.B5, R2.2
unnamed: LED1.O, LED2.I
unnamed: LED2.O, LED3.I
unnamed: LED3.O, LED4.I
unnamed: LED4.O, LED5.I
unnamed: LED5.O, LED6.I
unnamed: LED6.O, LED7.I
unnamed: LED8.I, LED9.O
unnamed: LED10.I, LED11.O
unnamed: LED9.I, LED10.O
unnamed: LED11.I, LED12.O
unnamed: LED12.I, LED13.O
unnamed: LED8.O, LED14.I
unnamed: LED14.O, LED15.I
unnamed: LED15.O, LED16.I
unnamed: LED16.O, LED17.I
unnamed: LED17.O, LED18.I
unnamed: LED18.O, LED19.I
unnamed: LED19.O, LED25.I
unnamed: LED20.I, LED21.O
unnamed: LED20.O, LED26.I
unnamed: LED21.I, LED22.O
unnamed: LED22.I, LED23.O
unnamed: LED23.I, LED24.O
unnamed: LED24.I, LED25.O
unnamed: LED26.O, LED27.I
unnamed: LED27.O, LED28.I
unnamed: LED28.O, LED29.I
unnamed: LED29.O, LED30.I
unnamed: LED30.O, LED31.I
unnamed: LED31.O, LED35.I
unnamed: LED32.I, LED33.I, LED34.O
unnamed: LED34.I, LED35.O
unnamed: R5.1, U1.20
unnamed: SW1.1, SW7.1, SW14.1, SW20.1
unnamed: SW4.1, SW10.1, SW17.1, SW23.1, SW28.1
unnamed: SW5.1, SW11.1, SW18.1, SW24.1, SW29.2
unnamed: SW6.1, SW12.1, SW19.1, SW25.1, SW26.2, SW30.1, SW31.S2
unnamed: SW2.1, SW8.1, SW15.1, SW21.1
unnamed: SW3.1, SW9.1, SW16.1, SW22.1, SW27.1
VBUS: C1.1, J3.A4, J3.A9, J3.B4, J3.B9, U2.1, U2.3
VCC: C2.1, C3.1, C4.1, C5.1, D29.1, L1.1, LED1.+, LED2.+, LED3.+, LED4.+, LED5.+, LED6.+, LED7.+, LED8.+, LED9.+, LED10.+, LED11.+, LED12.+, LED13.+, LED14.+, LED15.+, LED16.+, LED17.+, LED18.+, LED19.+, LED20.+, LED21.+, LED22.+, LED23.+, LED24.+, LED25.+, LED26.+, LED27.+, LED28.+, LED29.+, LED30.+, LED31.+, LED32.+, LED33.+, LED34.+, LED35.+, R3.2, U1.24, U1.36, U1.48, U2.5
VREF: C6.1, L1.2, U1.9
